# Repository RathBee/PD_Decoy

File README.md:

# PD_Decoy
A simple USB-PD triggering device

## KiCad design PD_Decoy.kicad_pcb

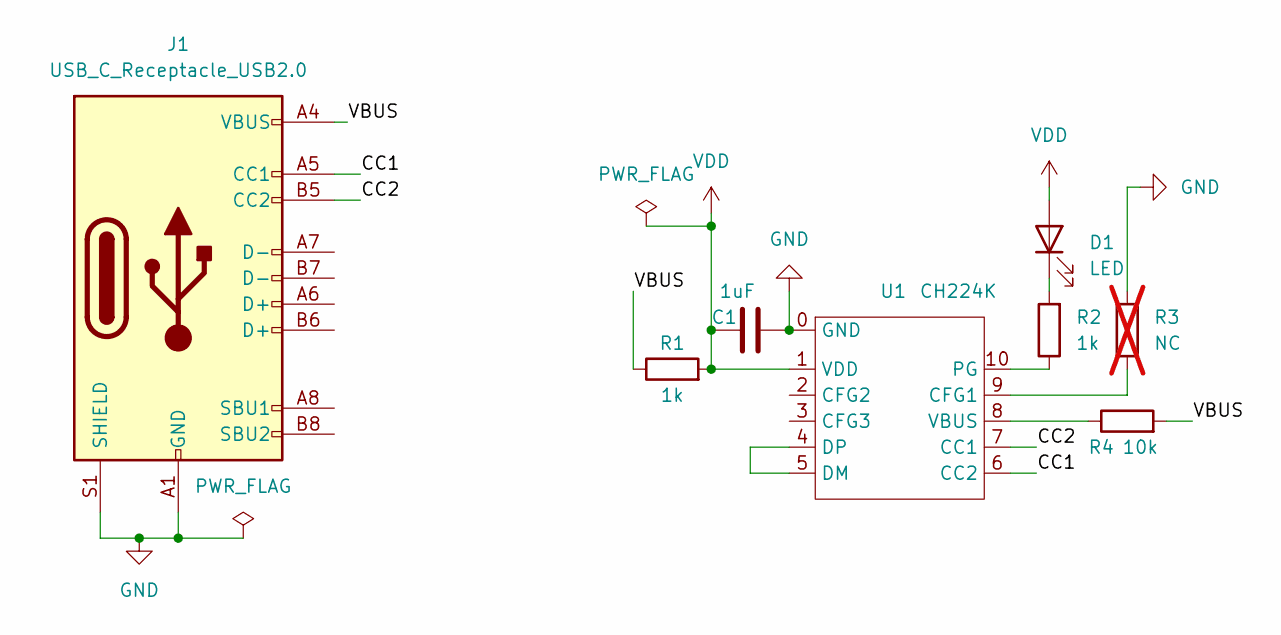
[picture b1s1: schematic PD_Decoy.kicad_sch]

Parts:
C1: 1uF; C_0805_2012Metric
D1: LED; LED_0805_2012Metric
J1: USB_C_Receptacle_USB2.0; USB_C_Receptacle_HRO_TYPE-C-31-M-12
R1: 1k; R_1210_3225Metric
R2: 1k; R_0805_2012Metric
R3: NC; R_0805_2012Metric; not fitted
R4: 10k; R_0805_2012Metric
U1: CH224K; ESSOP-10_L4.9-W3.9-P1.0-LS6.0-TL-EP

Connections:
/CC1: J1.A5 (CC1), U1.6 (CC2)
/CC2: J1.B5 (CC2), U1.7 (CC1)
/VBUS: J1.A4 (VBUS), J1.A9 (VBUS), J1.B4 (VBUS), J1.B9 (VBUS), R1.1, R4.2
GND: C1.2, J1.A1 (GND), J1.A12 (GND), J1.B1 (GND), J1.B12 (GND), J1.S1 (SHIELD), R3.1, U1.0 (GND)
unnamed: D1.1 (K), R2.2
unnamed: R3.2, U1.9 (CFG1)
unnamed: U1.4 (DP), U1.5 (DM)
unnamed: R2.1, U1.10 (PG)
unnamed: R4.1, U1.8 (VBUS)
VDD: C1.1, D1.2 (A), R1.2, U1.1 (VDD)

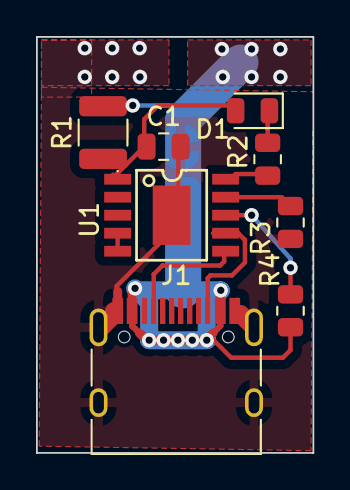
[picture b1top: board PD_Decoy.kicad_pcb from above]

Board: 2 copper layers, 15.4 x 23.1 mm, 8 parts (0 on the bottom side), 10 nets.

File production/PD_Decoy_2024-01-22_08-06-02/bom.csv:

Designator,Footprint,Quantity,Value,LCSC Part #
C1,0805,1,1uF,
D1,0805,1,LED,
J1,USB_C_Receptacle_HRO_TYPE-C-31-M-12,1,USB_C_Receptacle_USB2.0,
R1,1210,1,1k,
R2,0805,1,1k,
R4,0805,1,10k,
U1,ESSOP-10_L4.9-W3.9-P1.0-LS6.0-TL-EP,1,CH224K,

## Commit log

2024-01-22 configure gitignore
2024-01-22 License
2024-01-22 add a eye-catching picture to README
2024-01-22 remove gerber files
2024-01-22 line vias on VBUS and GND up a bit
2024-01-22 reroute and widen VBUS track for better current-carrying ability
2024-01-22 fix asymmetrical via placement
2024-01-24 Replace the picture in README for a newer one
